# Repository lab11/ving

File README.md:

Rumblecation
=======

Mobile phones have vibratory motors which can transmit vibration, and 
accelerometers, which can sense vibration. Rumblecation takes advantage
of this hardware to communicate over vibration. Vibratory communication
would limit the communication domain to two or more physically coupled
devices, and this could be used to pair a specific subset of devices
sharing a surface such as table. 

Custom hardware was developed to closely emulate the hardware found in
common smartphones. A simple protocol was then designed for vibratory
communication and firmware was developed for our hardware to implement
this protocol.

Current work is focused on improving data rate and reliability, which
should be achievable by improving the algorithms that are processing 
accelerometer data.

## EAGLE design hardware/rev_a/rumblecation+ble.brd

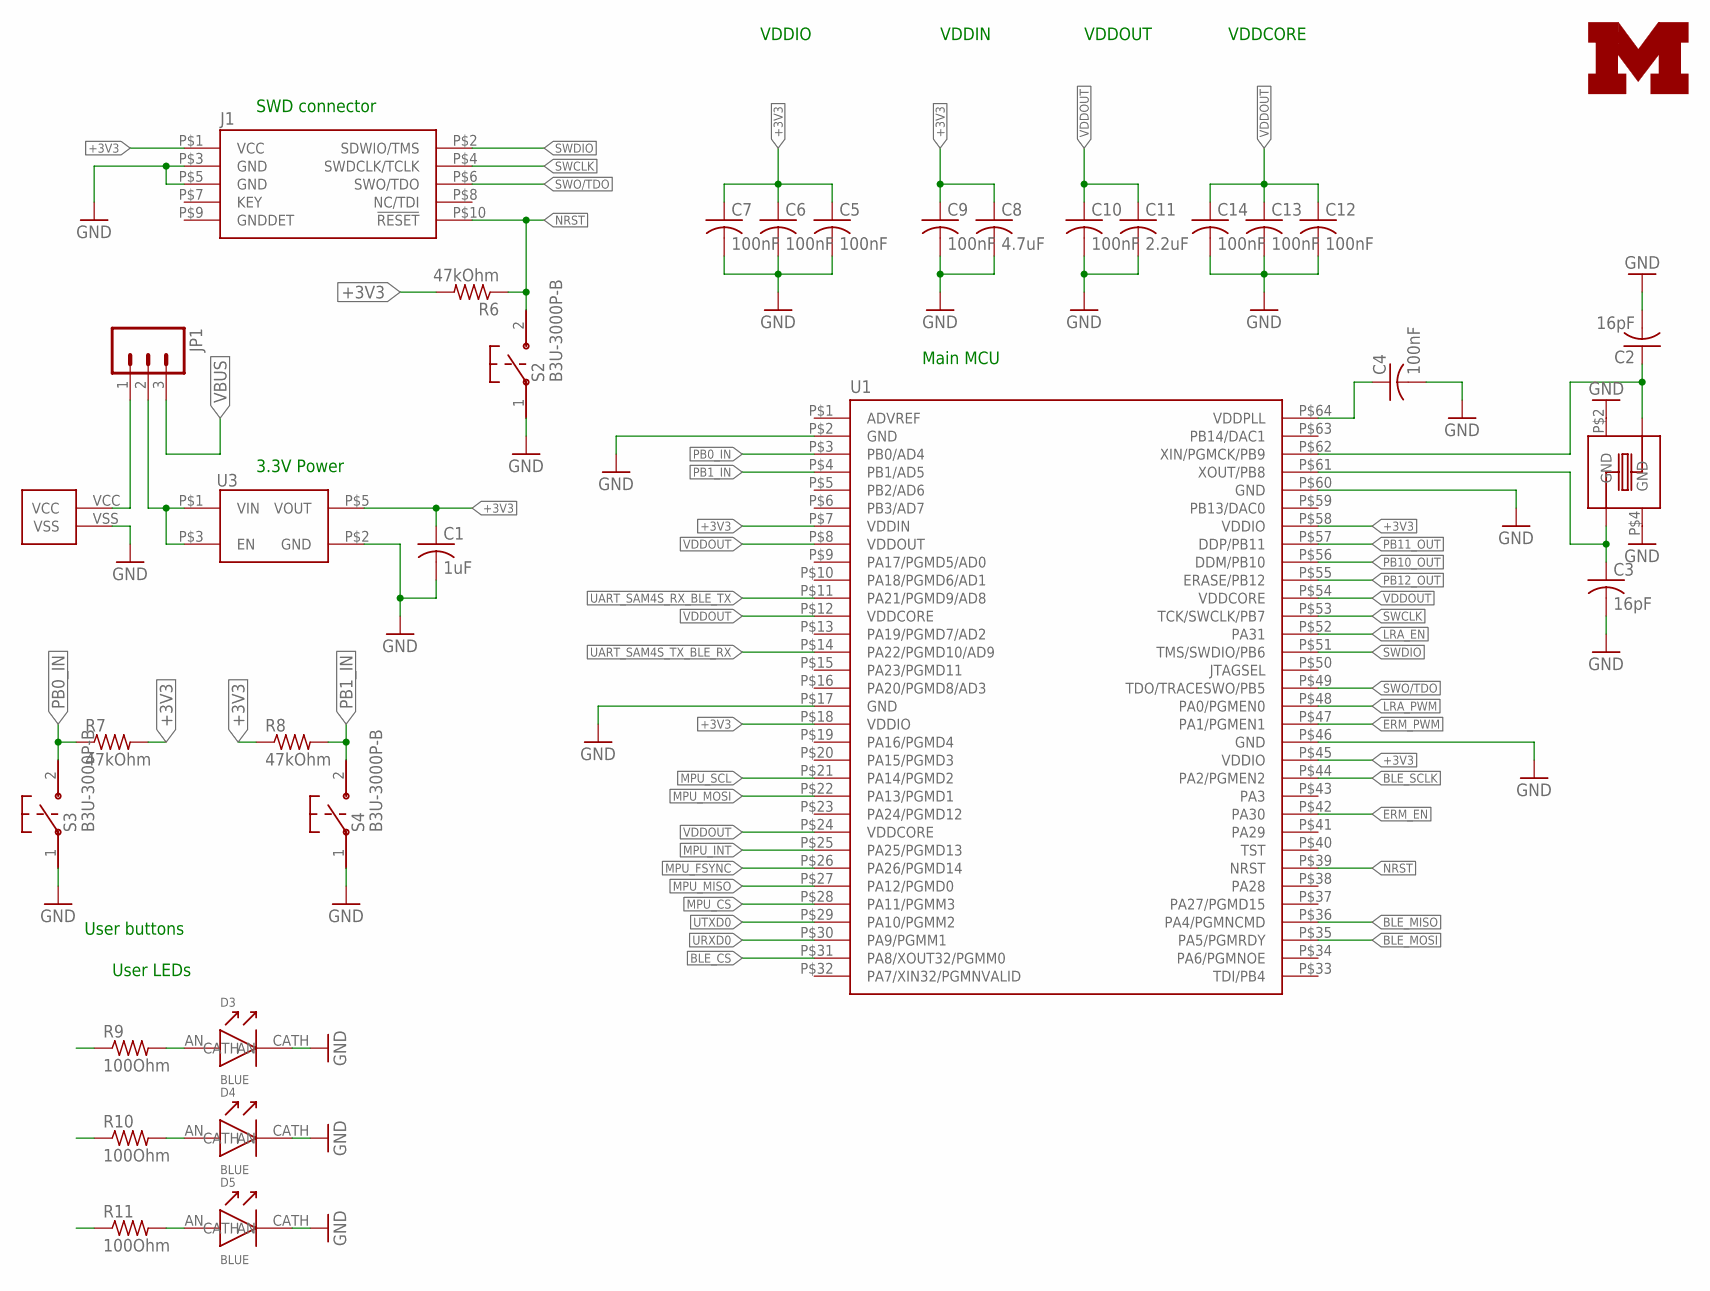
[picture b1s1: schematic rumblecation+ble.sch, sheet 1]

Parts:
C1: 1uF; C0402
C2, C3: 16pF; C0402
C4, C5, C6, C7, C9, C10, C12, C13, C14: 100nF; C0402
C8: 4.7uF; C0603
C11: 2.2uF; C0603
D3, D4, D5: BLUE; D0603
J1: FCI_CORTEX_SWD_CONNECTOR; FCI_10_PIN_SMD_0.5
J2: JST_S2B-PH-SM4-TB_CONNECTOR
JP1: M03PTH; 1X03
LOGO1: UMICH_SOLID_TINY; UMICH_SOLID_50MIL
R6, R7, R8: 47kOhm; R0402
R9, R10, R11: 100Ohm; R0402
S2, S3, S4: B3U-3000P-B
U1: ATSAM4S2BA-AU; ATMEL_10X10_QFP_64
U3: TLV73333PDBVT; TI_SOT-23-5
Y1: ECS_ECS-120-20-33-CKM-TR; ECS_ECX-32

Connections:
+3V3: C1.1, C5.1, C6.1, C7.1, C8.1, C9.1, J1.P$1 (VCC), R6.2, R7.2, R8.1, U1.P$7 (VDDIN), U1.P$18 (VDDIO), U1.P$45 (VDDIO), U1.P$58 (VDDIO), U3.P$5 (VOUT); also elsewhere on the board
BLE_CS: U1.P$31 (PA8/XOUT32/PGMM0); also elsewhere on the board
BLE_MISO: U1.P$36 (PA4/PGMNCMD); also elsewhere on the board
BLE_MOSI: U1.P$35 (PA5/PGMRDY); also elsewhere on the board
BLE_SCLK: U1.P$44 (PA2/PGMEN2); also elsewhere on the board
ERM_EN: U1.P$42 (PA30); also elsewhere on the board
ERM_PWM: U1.P$47 (PA1/PGMEN1); also elsewhere on the board
GND: C1.2, C2.2, C3.2, C4.2, C5.2, C6.2, C7.2, C8.2, C9.2, C10.2, C11.2, C12.2, C13.2, C14.2, D3.CATH, D4.CATH, D5.CATH, J1.P$3 (GND), J1.P$5 (GND), J2.VSS, S2.1, S3.1, S4.1, U1.P$2 (GND), U1.P$17 (GND), U1.P$46 (GND), U1.P$60 (GND), U3.P$2 (GND), Y1.P$2 (GND), Y1.P$4 (GND); also elsewhere on the board
LRA_EN: U1.P$52 (PA31); also elsewhere on the board
LRA_PWM: U1.P$48 (PA0/PGMEN0); also elsewhere on the board
MPU_CS: U1.P$28 (PA11/PGMM3); also elsewhere on the board
MPU_FSYNC: U1.P$26 (PA26/PGMD14); also elsewhere on the board
MPU_INT: U1.P$25 (PA25/PGMD13); also elsewhere on the board
MPU_MISO: U1.P$27 (PA12/PGMD0); also elsewhere on the board
MPU_MOSI: U1.P$22 (PA13/PGMD1); also elsewhere on the board
MPU_SCL: U1.P$21 (PA14/PGMD2); also elsewhere on the board
unnamed: JP1.2, U3.P$1 (VIN), U3.P$3 (EN)
unnamed: C4.1, U1.P$64 (VDDPLL)
unnamed: J2.VCC, JP1.1
unnamed: D3.AN, R9.2
unnamed: D4.AN, R10.2
unnamed: D5.AN, R11.2
NRST: J1.P$10 (!RESET!), R6.1, S2.2, U1.P$39 (NRST)
PB0_IN: R7.1, S3.2, U1.P$3 (PB0/AD4)
PB1_IN: R8.2, S4.2, U1.P$4 (PB1/AD5)
PB10_OUT: R10.1, U1.P$56 (DDM/PB10)
PB11_OUT: R9.1, U1.P$57 (DDP/PB11)
PB12_OUT: R11.1, U1.P$55 (ERASE/PB12)
SWCLK: J1.P$4 (SWDCLK/TCLK), U1.P$53 (TCK/SWCLK/PB7)
SWDIO: J1.P$2 (SDWIO/TMS), U1.P$51 (TMS/SWDIO/PB6)
SWO/TDO: J1.P$6 (SWO/TDO), U1.P$49 (TDO/TRACESWO/PB5)
UART_SAM4S_RX_BLE_TX: U1.P$11 (PA21/PGMD9/AD8); also elsewhere on the board
UART_SAM4S_TX_BLE_RX: U1.P$14 (PA22/PGMD10/AD9); also elsewhere on the board
URXD0: U1.P$30 (PA9/PGMM1); also elsewhere on the board
UTXD0: U1.P$29 (PA10/PGMM2); also elsewhere on the board
VBUS: JP1.3; also elsewhere on the board
VDDOUT: C10.1, C11.1, C12.1, C13.1, C14.1, U1.P$8 (VDDOUT), U1.P$12 (VDDCORE), U1.P$24 (VDDCORE), U1.P$54 (VDDCORE)
XIN: C2.1, U1.P$62 (XIN/PGMCK/PB9), Y1.P$1
XOUT: C3.1, U1.P$61 (XOUT/PB8), Y1.P$3

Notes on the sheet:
VDDIN
VDDOUT
VDDIO
VDDCORE
3.3V Power
SWD connector
Main MCU
User buttons
User LEDs

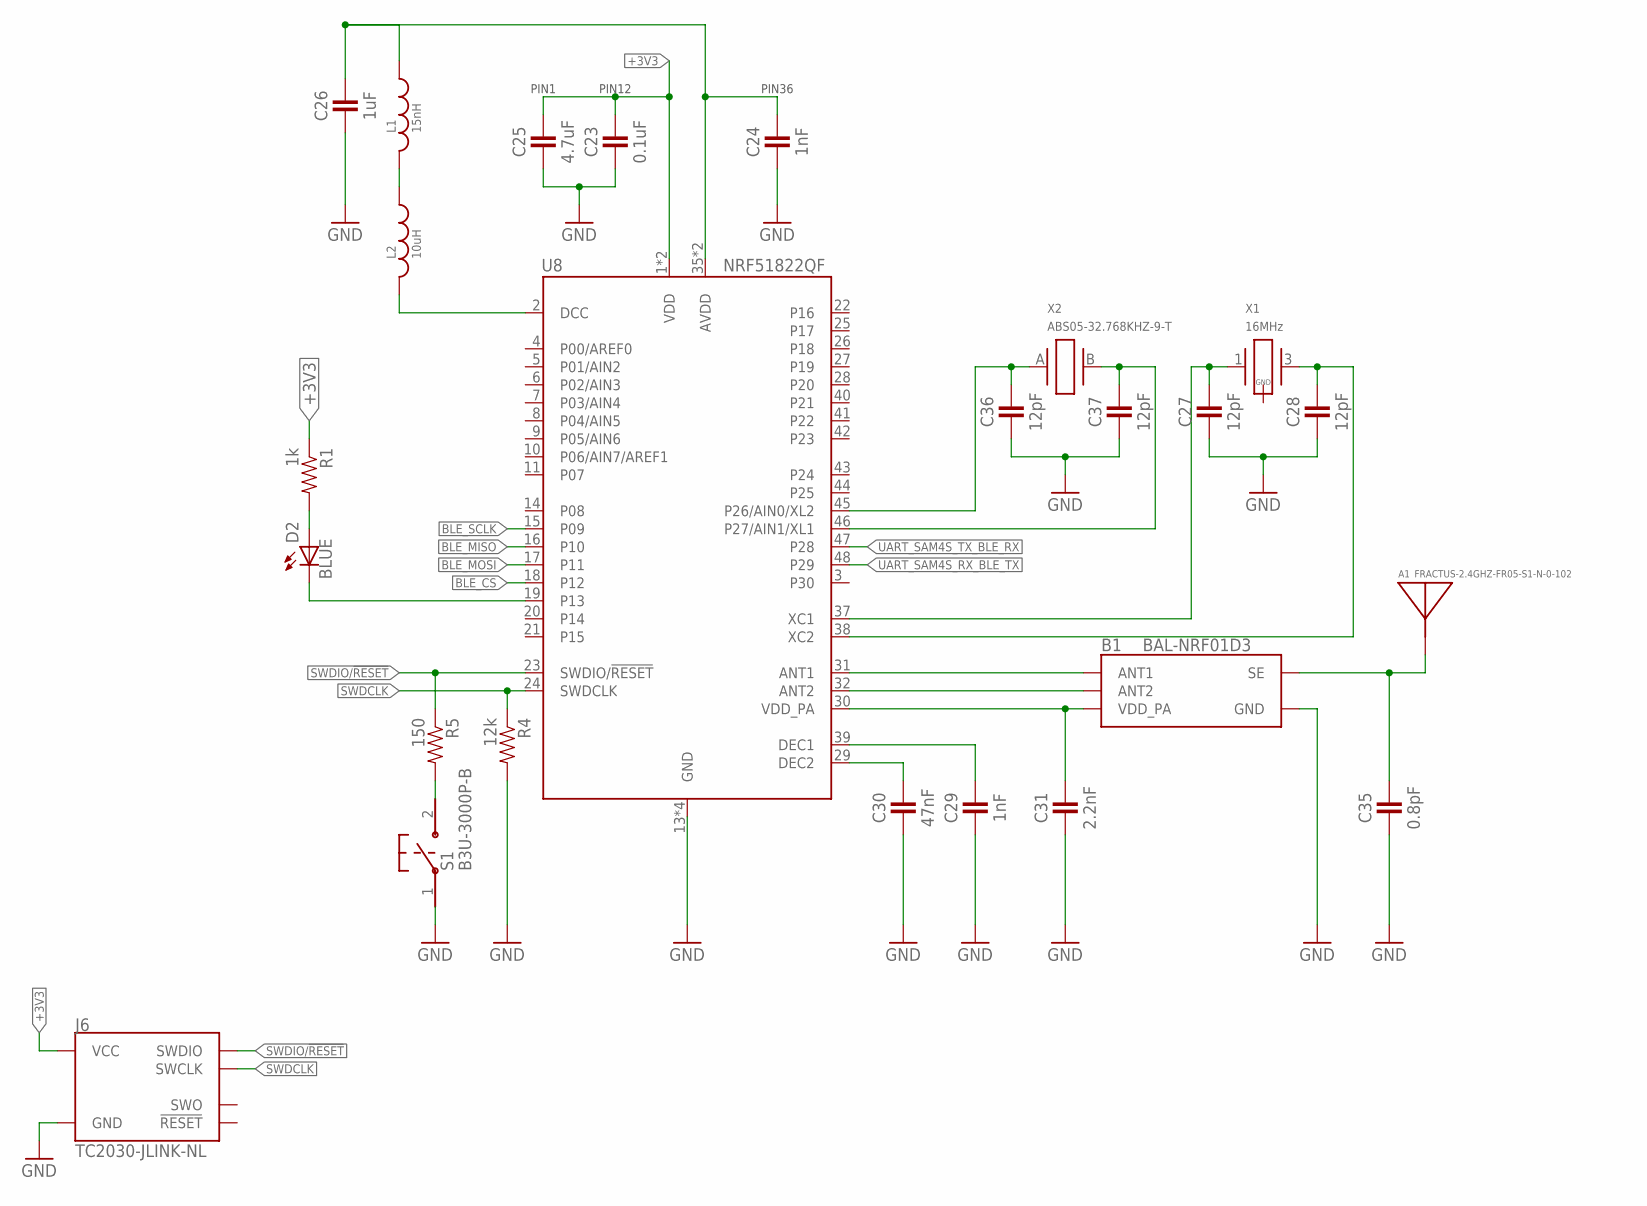
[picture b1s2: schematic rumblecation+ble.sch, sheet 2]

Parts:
A1: FRACTUS-2.4GHZ-FR05-S1-N-0-102; FRACTUS-ANTENNA-FR05-S1-N-0-102
B1: BAL-NRF01D3
C23: 0.1uF; 0402_CAP; DIGIKEY 445-4952-1-ND
C24, C29: 1nF; 0402_CAP; DIGIKEY 490-1303-1-ND
C25: 4.7uF; 0402_CAP; DIGIKEY 445-5947-1-ND
C26: 1uF; 0402_CAP; DIGIKEY 1276-1513-1-ND
C27, C28, C36, C37: 12pF; 0402_CAP; DIGIKEY 490-6197-1-ND
C30: 47nF; 0402_CAP; DIGIKEY 445-1264-1-ND
C31: 2.2nF; 0402_CAP; DIGIKEY 490-5419-1-ND
C35: 0.8pF; 0402_CAP; DIGIKEY 490-6269-1-ND
D2: BLUE; LED-0603
J6: TC2030-JLINK-NL; TC2030-IDC-NL
L1: 15nH; 0402_CAP; DIGIKEY 587-1521-1-ND
L2: 10uH; 0603_CAP; DIGIKEY 490-4025-1-ND
R1: 1k; 0402_RES; DIGIKEY RHM1.0KCECT-ND
R4: 12k; 0402_RES; DIGIKEY RHM12.0KCDCT-ND
R5: 150; 0402_RES; DIGIKEY RHM150CDCT-ND
S1: B3U-3000P-B
U8: NRF51822QF; QFN-48-6MM
X1: 16MHz; TXC-8Y; DIGIKEY 887-2003-1-ND
X2: ABS05-32.768KHZ-9-T; ABS05

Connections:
+3V3: C23.1, C25.1, J6.1 (VCC), R1.1, U8.1 (VDD), U8.12 (VDD); also elsewhere on the board
A0: C36.1, U8.45 (P26/AIN0/XL2), X2.A (1)
A1: C37.1, U8.46 (P27/AIN1/XL1), X2.B (2)
AVDD: C24.1, C26.1, L1.1, U8.35 (AVDD), U8.36 (AVDD)
BLE_CS: U8.18 (P12); also elsewhere on the board
BLE_MISO: U8.16 (P10); also elsewhere on the board
BLE_MOSI: U8.17 (P11); also elsewhere on the board
BLE_SCLK: U8.15 (P09); also elsewhere on the board
DCC: L2.2, U8.2 (DCC)
GND: B1.GND, C23.2, C24.2, C25.2, C26.2, C27.2, C28.2, C29.2, C30.2, C31.2, C35.2, C36.2, C37.2, J6.5 (GND), R4.2, S1.1, U8.13 (GND), U8.33 (GND), U8.34 (GND), U8.GND; also elsewhere on the board
unnamed: B1.ANT1, U8.31 (ANT1)
unnamed: B1.ANT2, U8.32 (ANT2)
unnamed: A1.1, B1.SE, C35.1
unnamed: L1.2, L2.1
unnamed: D2.C, U8.19 (P13)
unnamed: C27.1, U8.37 (XC1), X1.1
unnamed: C28.1, U8.38 (XC2), X1.3 (2)
unnamed: C29.1, U8.39 (DEC1)
unnamed: C30.1, U8.29 (DEC2)
unnamed: R5.2, S1.2
unnamed: D2.A, R1.2
SWDCLK: J6.4 (SWCLK), R4.1, U8.24 (SWDCLK)
SWDIO/!RESET: J6.2 (SWDIO), R5.1, U8.23 (SWDIO/!RESET)
UART_SAM4S_RX_BLE_TX: U8.48 (P29); also elsewhere on the board
UART_SAM4S_TX_BLE_RX: U8.47 (P28); also elsewhere on the board
VDD_PA: B1.VCC (VDD_PA), C31.1, U8.30 (VDD_PA)

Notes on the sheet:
PIN12
PIN1
PIN36

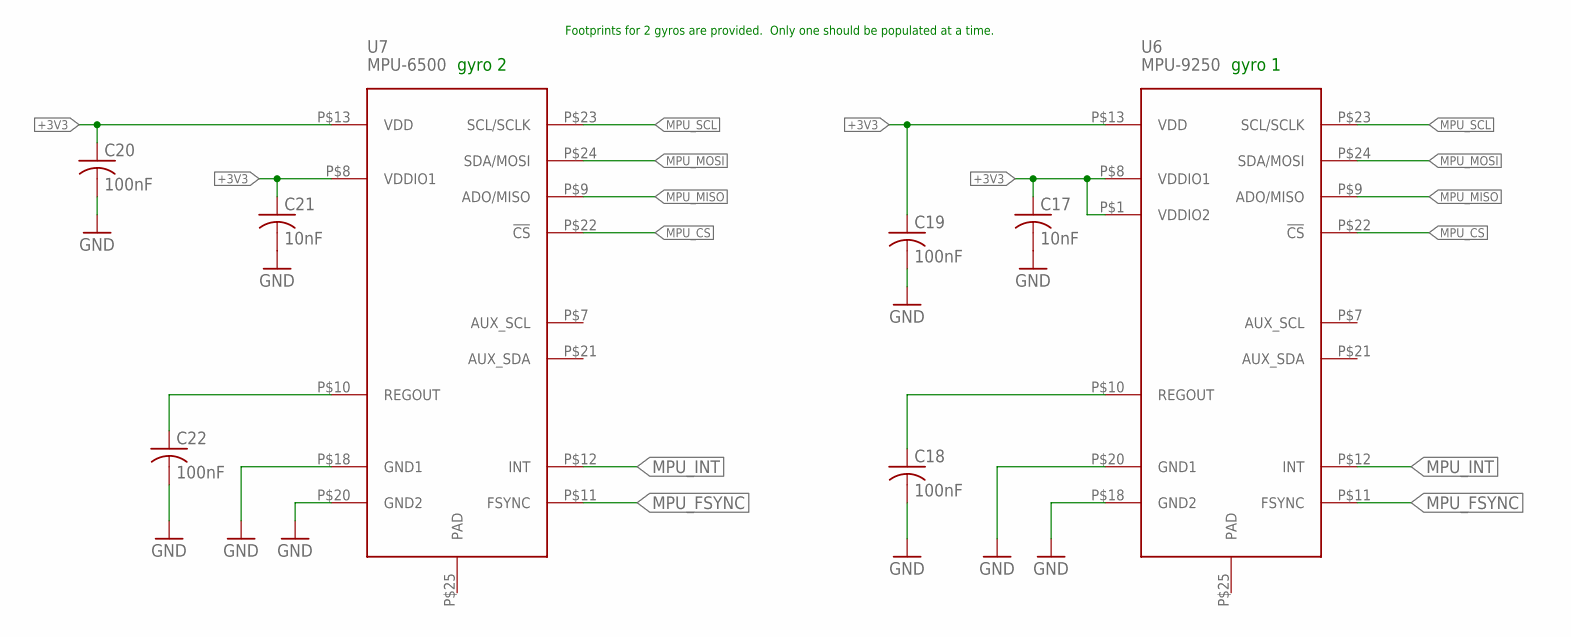
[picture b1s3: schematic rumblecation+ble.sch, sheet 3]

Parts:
C17, C21: 10nF; C0402
C18, C19, C20, C22: 100nF; C0402
U6: MPU-9250; MPU-9X50
U7: MPU-6500; MPU-9X50

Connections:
+3V3: C17.1, C19.1, C20.1, C21.1, C22.1, U6.P$1 (VDDIO2), U6.P$8 (VDDIO1), U6.P$13 (VDD), U7.P$8 (VDDIO1), U7.P$10 (REGOUT), U7.P$13 (VDD); also elsewhere on the board
GND: C17.2, C18.2, C19.2, C20.2, C21.2, C22.2, U6.P$18 (GND2), U6.P$20 (GND1), U7.P$18 (GND1), U7.P$20 (GND2); also elsewhere on the board
MPU_CS: U6.P$22 (!CS), U7.P$22 (!CS); also elsewhere on the board
MPU_FSYNC: U6.P$11 (FSYNC), U7.P$11 (FSYNC); also elsewhere on the board
MPU_INT: U6.P$12 (INT), U7.P$12 (INT); also elsewhere on the board
MPU_MISO: U6.P$9 (ADO/MISO), U7.P$9 (ADO/MISO); also elsewhere on the board
MPU_MOSI: U6.P$24 (SDA/MOSI), U7.P$24 (SDA/MOSI); also elsewhere on the board
MPU_SCL: U6.P$23 (SCL/SCLK), U7.P$23 (SCL/SCLK); also elsewhere on the board
unnamed: C18.1, U6.P$10 (REGOUT)

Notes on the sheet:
gyro 1
gyro 2
Footprints for 2 gyros are provided. Only one should be populated at a time.

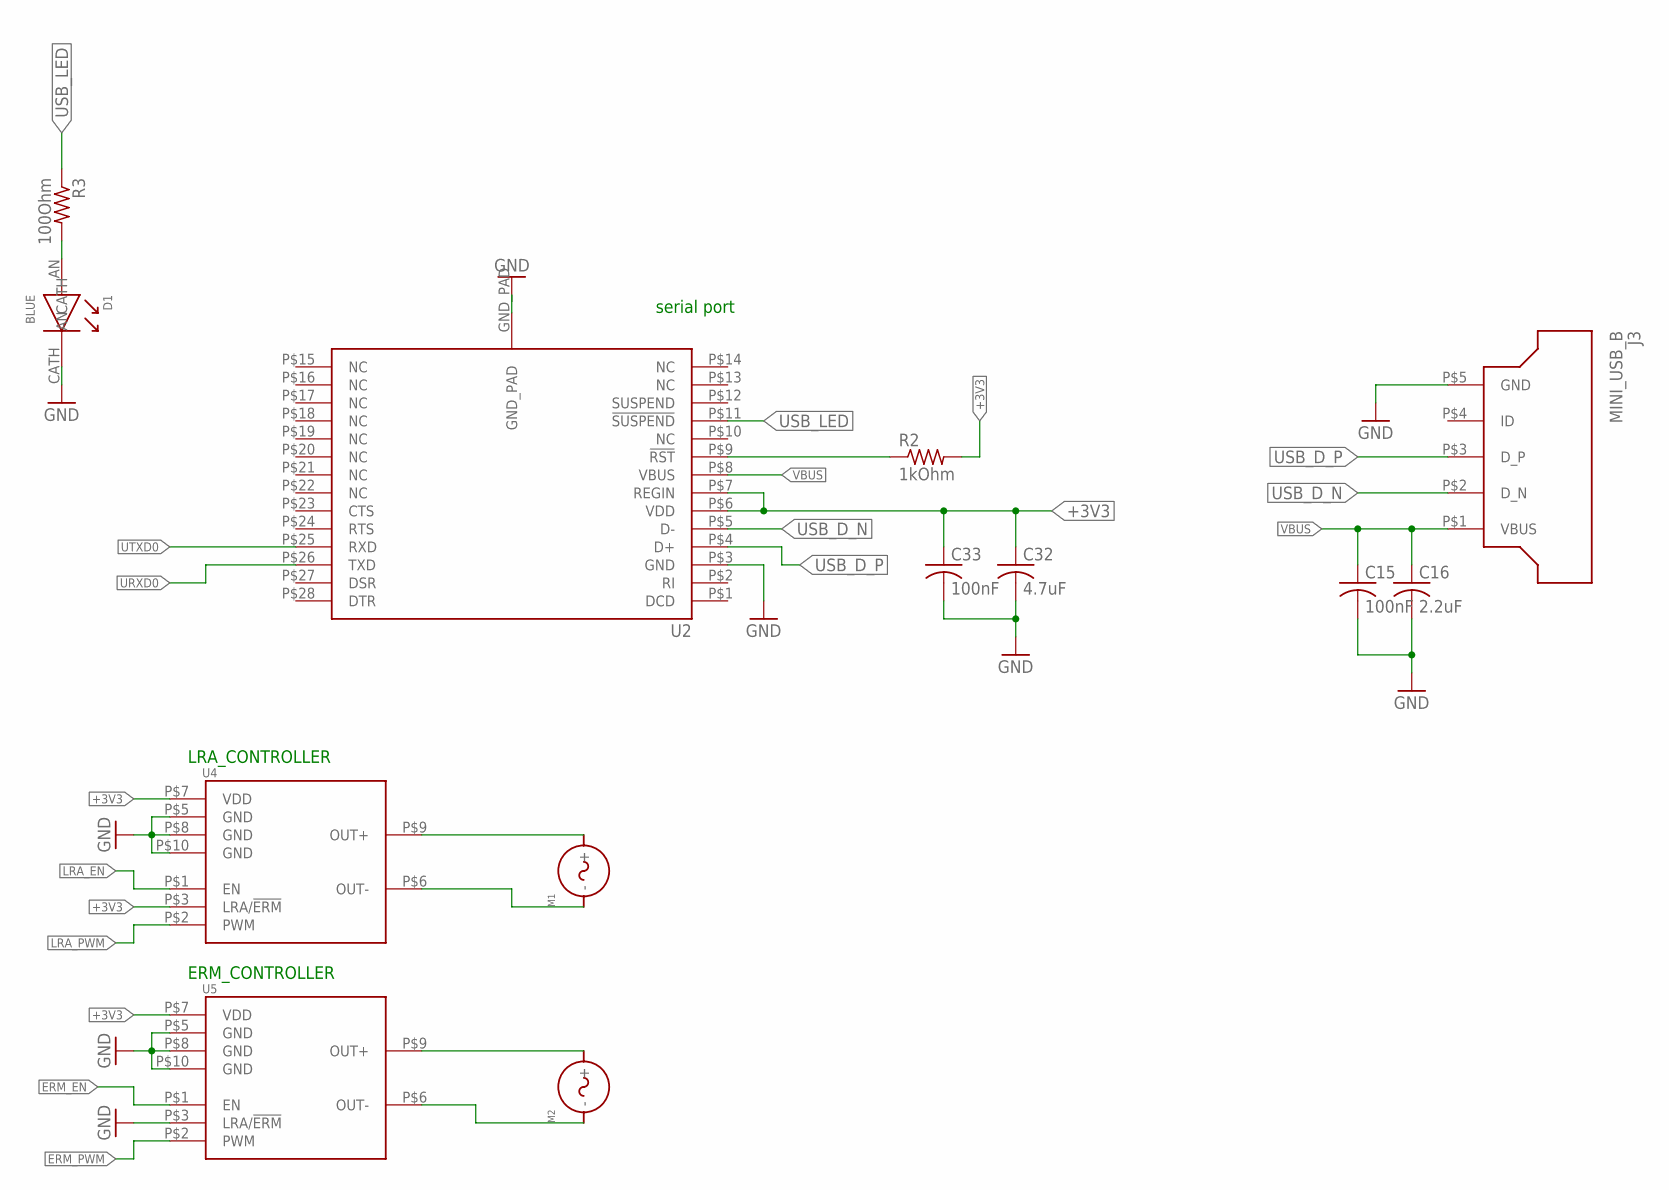
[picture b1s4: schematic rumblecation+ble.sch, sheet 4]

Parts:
C15, C33: 100nF; C0402
C16: 2.2uF; C0402
C32: 4.7uF; C0402
D1: BLUE; D0603
J3: MINI_USB_B; UX60SC-MB-5ST
M1: PRECISION_MICRODRIVES_C100-10; PRECISION_MICRODRIVES_10MM
M2: PRECISION_MICRODRIVES_310-113; PRECISION_MICRODRIVES_10MM
R2: 1kOhm; R0402
R3: 100Ohm; R0402
U2: SILABS_CP2102; SILABS_QFN28
U4, U5: TI_DRV2603; TI_S-PWQFN-N10

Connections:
+3V3: C32.1, C33.1, R2.2, U2.P$6 (VDD), U2.P$7 (REGIN), U4.P$3 (LRA/!ERM!), U4.P$7 (VDD), U5.P$7 (VDD); also elsewhere on the board
ERM_EN: U5.P$1 (EN); also elsewhere on the board
ERM_PWM: U5.P$2 (PWM); also elsewhere on the board
GND: C15.2, C16.2, C32.2, C33.2, D1.CATH, J3.P$5 (GND), U2.GND_PAD, U2.P$3 (GND), U4.P$5 (GND), U4.P$8 (GND), U4.P$10 (GND), U5.P$3 (LRA/!ERM!), U5.P$5 (GND), U5.P$8 (GND), U5.P$10 (GND); also elsewhere on the board
LRA_EN: U4.P$1 (EN); also elsewhere on the board
LRA_PWM: U4.P$2 (PWM); also elsewhere on the board
unnamed: R2.1, U2.P$9 (!RST!)
unnamed: M1.P$1 (-), U4.P$6 (OUT-)
unnamed: M1.P$2 (+), U4.P$9 (OUT+)
unnamed: D1.AN, R3.2
unnamed: M2.P$2 (+), U5.P$9 (OUT+)
unnamed: M2.P$1 (-), U5.P$6 (OUT-)
URXD0: U2.P$26 (TXD); also elsewhere on the board
USB_D_N: J3.P$2 (D_N), U2.P$5 (D-)
USB_D_P: J3.P$3 (D_P), U2.P$4 (D+)
USB_LED: R3.1, U2.P$11 (!SUSPEND!)
UTXD0: U2.P$25 (RXD); also elsewhere on the board
VBUS: C15.1, C16.1, J3.P$1 (VBUS), U2.P$8 (VBUS); also elsewhere on the board

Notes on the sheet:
LRA_CONTROLLER
ERM_CONTROLLER
serial port

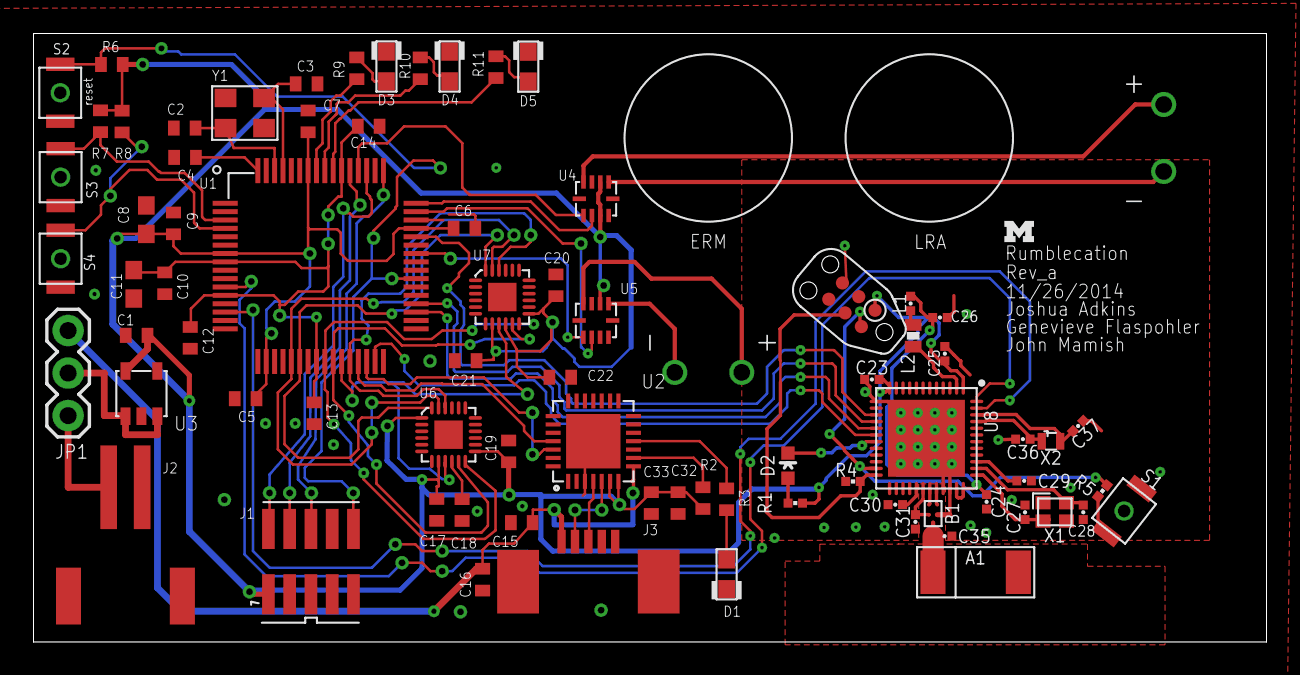
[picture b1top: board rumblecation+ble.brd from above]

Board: 2 copper layers, 73.6 x 36.3 mm, 79 parts (0 on the bottom side), 67 nets.

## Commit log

2014-11-14 Arduino MPU driver
2014-11-19 changed
2014-11-21 Made new I2c Sketch
2014-11-21 fixed I2c test file
2014-11-21 fixed i2c test compiler error
2014-11-21 Python FFT Visulizer added and python scripts
2014-11-25 Added nodewebkit graphing application
2014-11-25 Added rumblcation+ ble board and schematic
2014-11-26 Added newest board, schematic and lib files. Updated visualization file
2014-11-26 Fixed directory organization
2014-11-26 removed graphing to another repo
2014-11-26 Added newest fft_test code
2014-11-26 Fixed SPI bus
2014-11-26 fixed silab usb-uart, added fsync and int to accell, updated schematic prettiness, fixed regout on accel
2014-11-26 Added a power selector header, fixed some routing errors
2014-11-26 Final board revision - being sent for production
2014-12-03 Main file to initialize SP iand read from the MPU6500
2014-12-04 FFT + timable interrupts, functional
2014-12-04 added mangitude and max frequency peak finding at 1000Hz
2014-12-04 added shift left functionality and performed FFT with every new sample, as opposed to the previous code that only ran the FFT when the buffer filled with the ful FFT_SIZE*2 samples
2014-12-05 FFT and SPI for SAM4S4B
2014-12-06 Added PWM, FFT, Interrupt, SPI - motors in turned off state
2014-12-06 Updated to pulse motor at frequency and sample at freq
2014-12-07 Most recent, has TX and rX mode and can interperit a bit string
2014-12-07 broken attempt at recieve/transmistter communitoin, dynamic level settting, and frame syncronizatin
2014-12-07 Working self- transmit post processing code at 120MHz
2014-12-07 working, self transmits, post processor, with speed opitimzations and only a single complex magnitude calculation
2014-12-08 Ttrying real time, fail, commented out
2014-12-08 Added main with simple uart calls and rumblecation application level driver
2014-12-08 some hold files and a working FFT, vibratory communication with applicatoin layer interface
2014-12-08 working final version
2014-12-17 Added README file
2015-04-23 added media and updated readme
2015-04-23 fixed README

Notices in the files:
parts and their libraries:
SparkFun-LED: Licensing: CC v3.0 Share-Alike You are welcome to use this library for commercial purposes.
